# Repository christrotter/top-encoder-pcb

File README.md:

# Overview
mk22 top encoders have a 5mm mouse wheel encoder and four leds.

This pcb is designed to fit inside the 30x15mm encoder wheel.  Why?  So we can shine leds up through the single-wall TPU covering, and so indicate what function the encoder is providing.  It requires the use of 5mm mouse encoders - otherwise the 30mm diameter wheel is too small...and at 30mm, we're already pushing the boundaries of what packaging will allow.

There is a de-noise circuit thingy, inherited from here: https://github.com/christrotter/mouse-encoder-pcb

The FFC connector will hook into the mainboard's giant FFC - see [schematic section](#schematic) for pinout.

## Bill of Materials (BOM)
| Designator | Footprint | Quantity | Value | LCSC Part # |
|-----------------------------|--------------------------|----------|-----------------|--------------|
| C1, C2 | 0402 | 2 | 0.01uF | |
| P1 | FPC-SMD_AFC01-S12FCA-00 | 1 | AFC01-S12FCA-00 | C262661 |
| R1, R2 | 0402 | 2 | 330 | |
| R3, R4 | 0402 | 2 | 10k | |
| U1, U2, U3, U8 | LED-SMD_4P-L1.4-W1.4-TL | 4 | SK6805-EC14_C2909055 | C2909055 |

## Prototype mounting
Uh, ignore the gold silk PLA - just using up rando spools for prototyping.

# Schematic

# PCB layout

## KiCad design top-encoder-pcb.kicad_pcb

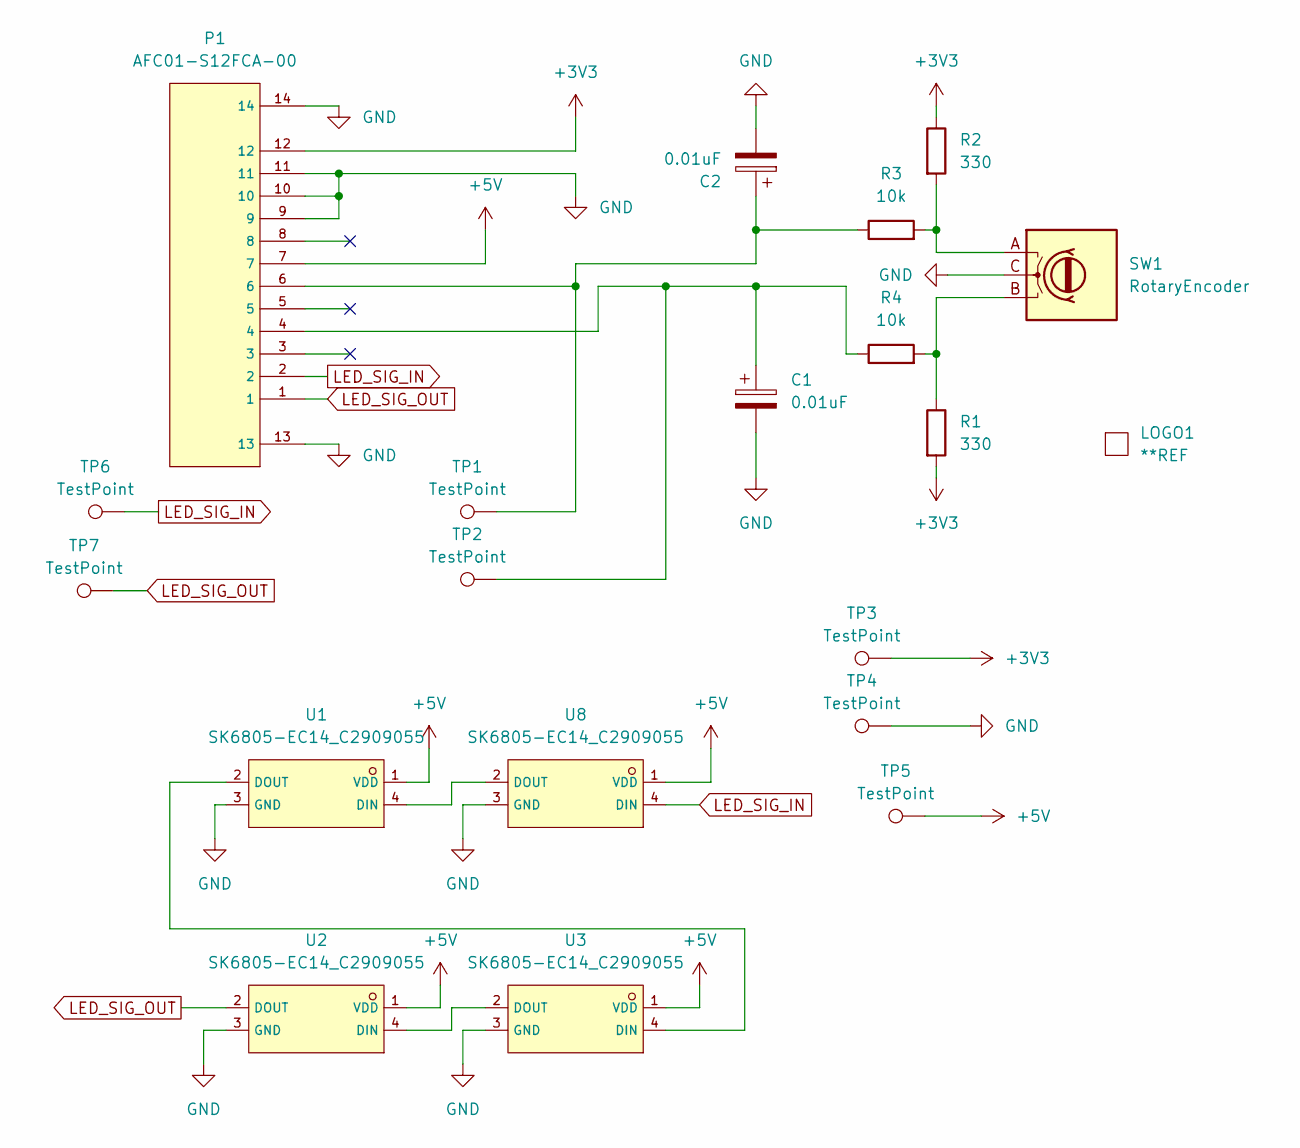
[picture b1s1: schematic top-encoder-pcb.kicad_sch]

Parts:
C1, C2: 0.01uF; C_0402_1005Metric
LOGO1: **REF; awesome-logo
P1: AFC01-S12FCA-00; FPC-SMD_AFC01-S12FCA-00; LCSC C262661
R1, R2: 330; R_0402_1005Metric
R3, R4: 10k; R_0402_1005Metric
SW1: RotaryEncoder; SW-TH_EC10EXXXXXXX
TP1, TP2, TP3, TP4, TP5, TP6, TP7: TestPoint; TestPoint_Pad_D1.0mm
U1, U2, U3, U8: SK6805-EC14_C2909055; LED-SMD_4P-L1.4-W1.4-TL; LCSC C2909055

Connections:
+3V3: P1.12, R1.2, R2.1, TP3.1
+5V: P1.7, TP5.1, U1.1 (VDD), U2.1 (VDD), U3.1 (VDD), U8.1 (VDD)
GND: C1.2, C2.2, P1.9, P1.10, P1.11, P1.13, P1.14, SW1.C, TP4.1, U1.3 (GND), U2.3 (GND), U3.3 (GND), U8.3 (GND)
LED_SIG_IN: P1.2, TP6.1, U8.4 (DIN)
LED_SIG_OUT: P1.1, TP7.1, U2.2 (DOUT)
unnamed: C1.1, P1.4, R4.1, TP2.1
unnamed: C2.1, P1.6, R3.1, TP1.1
unnamed: R1.1, R4.2, SW1.B
unnamed: R2.2, R3.2, SW1.A
unnamed: U1.4 (DIN), U8.2 (DOUT)
unnamed: U1.2 (DOUT), U3.4 (DIN)
unnamed: U2.4 (DIN), U3.2 (DOUT)

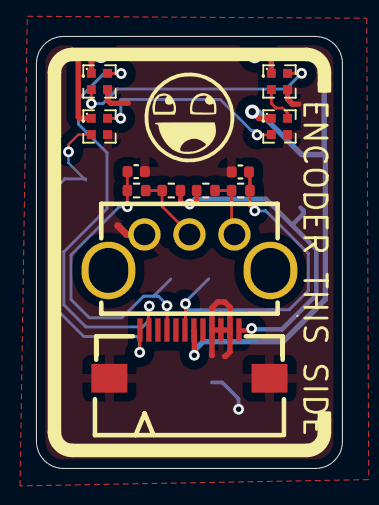
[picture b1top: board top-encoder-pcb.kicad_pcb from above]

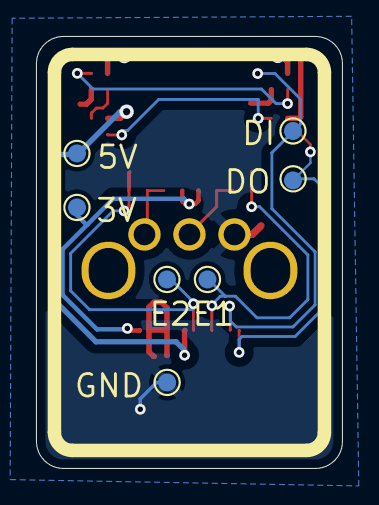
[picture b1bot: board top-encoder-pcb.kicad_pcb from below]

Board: 2 copper layers, 17.0 x 24.0 mm, 20 parts (7 on the bottom side), 12 nets.

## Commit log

2026-04-19 rev2 readme updates
